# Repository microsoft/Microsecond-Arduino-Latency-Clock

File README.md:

# Microsecond Arduino Due Code and Schematics

Microsecond Arduino Due Code and Schematics accompanying the paper presented in IEEE VR 2020 "Measuring System Visual Latency through Cognitive Latency on Video See-Through AR devices" [1]
https://www.microsoft.com/en-us/research/publication/measuring-system-visual-latency-through-cognitive-latency-on-video-see-through-ar-devices/

The clock starts from zero and continues to displayelapsed time since the device was powered on. The LED turn-on andturn-off time is sub-microsecond [2], therefore we know that ourclock is sufficient for at least 0.1 millisecond measurements as theLEDs turn on and off faster than we are updating the digit segments.

This clock can be then visualized through an external observer [3] using high refresh cameras.

[1] Gruen, R., Ofek, E., Steed, A., Gal, R., Sinclair, M., & Gonzalez-Franco, M. (2020) Measuring System Visual Latency through Cognitive Latency on Video See-Through AR devices. IEEE VR 2020

[2] Lee,T. P. (1975) Effect of junction capacitance on the rise time of led’s and onthe turn-on delay of injection lasers. The Bell System Technical Journal,54(1):53–68, Jan 1975.

[3] Wu, W., Dong, Y., & Hoover, A. (2013). Measuring digital system latency from sensing to actuation at continuous 1-ms resolution. Presence: Teleoperators and Virtual Environments, 22(1), 20-35.

Schematics created with Eagle v 9.5.2.

# Contributing

This project welcomes contributions and suggestions.  Most contributions require you to agree to a
Contributor License Agreement (CLA) declaring that you have the right to, and actually do, grant us
the rights to use your contribution. For details, visit https://cla.opensource.microsoft.com.

When you submit a pull request, a CLA bot will automatically determine whether you need to provide
a CLA and decorate the PR appropriately (e.g., status check, comment). Simply follow the instructions
provided by the bot. You will only need to do this once across all repos using our CLA.

This project has adopted the [Microsoft Open Source Code of Conduct](https://opensource.microsoft.com/codeofconduct/).
For more information see the [Code of Conduct FAQ](https://opensource.microsoft.com/codeofconduct/faq/) or
contact [opencode@microsoft.com](mailto:opencode@microsoft.com) with any additional questions or comments.

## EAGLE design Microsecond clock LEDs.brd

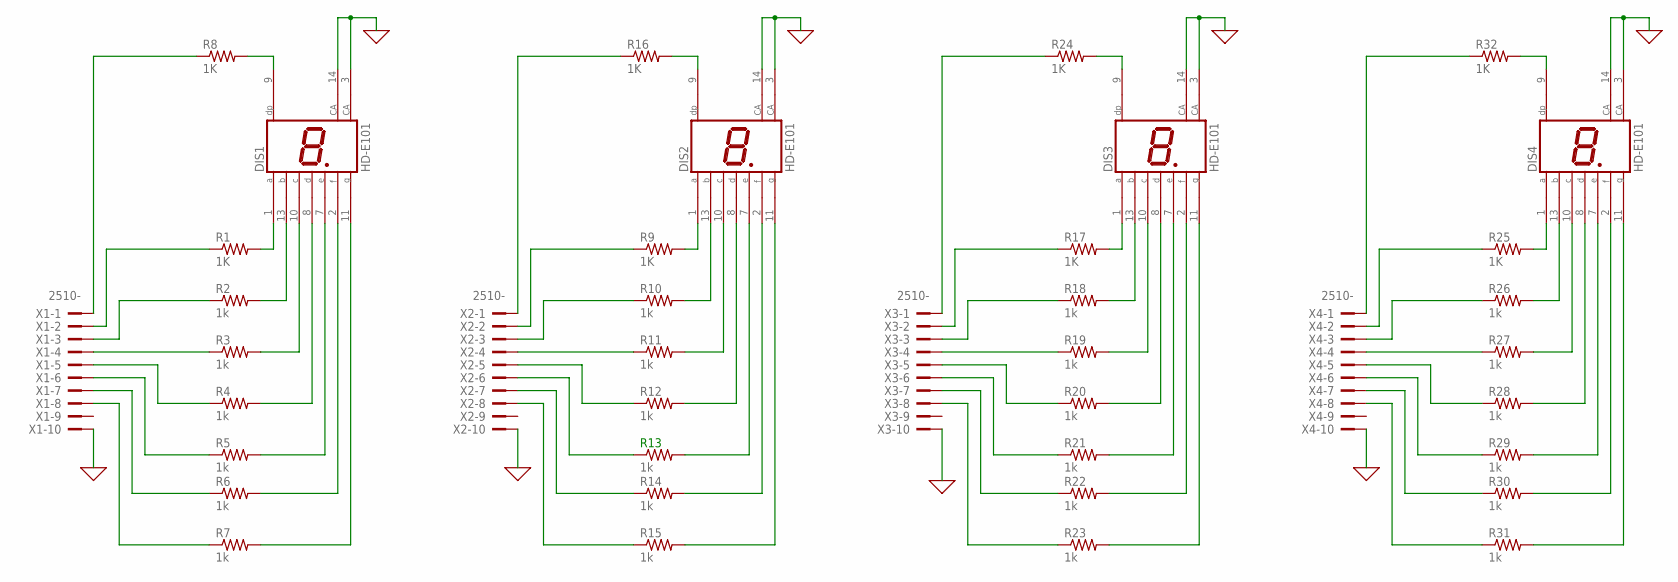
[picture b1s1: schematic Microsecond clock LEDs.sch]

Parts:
DIS1, DIS2, DIS3, DIS4: HD-E101; HDSP-I
R1, R8, R9, R16, R17, R24, R25, R32: 1K; 0207/7
R2, R3, R4, R5, R6, R7, R10, R11, R12, R13, R14, R15, R18, R19, R20, R21, R22, R23, R26, R27, R28, R29, R30, R31: 1k; 0207/7
X1, X2, X3, X4: 2510-; PAK100/2500-10

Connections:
0: DIS1.3 (CA), DIS1.14 (CA), DIS2.3 (CA), DIS2.14 (CA), DIS3.3 (CA), DIS3.14 (CA), DIS4.3 (CA), DIS4.14 (CA), X1.10, X2.10, X3.10, X4.10
unnamed: DIS1.1 (A), R1.2
unnamed: DIS1.13 (B), R2.2
unnamed: DIS1.10 (C), R3.2
unnamed: DIS1.8 (D), R4.2
unnamed: DIS1.7 (E), R5.2
unnamed: DIS1.2 (F), R6.2
unnamed: DIS1.11 (G), R7.2
unnamed: DIS1.9 (DP), R8.2
unnamed: R8.1, X1.1
unnamed: R1.1, X1.2
unnamed: R2.1, X1.3
unnamed: R3.1, X1.4
unnamed: R4.1, X1.5
unnamed: R5.1, X1.6
unnamed: R6.1, X1.7
unnamed: R7.1, X1.8
unnamed: DIS2.1 (A), R9.2
unnamed: DIS2.13 (B), R10.2
unnamed: DIS2.10 (C), R11.2
unnamed: DIS2.8 (D), R12.2
unnamed: DIS2.7 (E), R13.2
unnamed: DIS2.2 (F), R14.2
unnamed: DIS2.11 (G), R15.2
unnamed: DIS2.9 (DP), R16.2
unnamed: R16.1, X2.1
unnamed: R9.1, X2.2
unnamed: R10.1, X2.3
unnamed: R11.1, X2.4
unnamed: R12.1, X2.5
unnamed: R13.1, X2.6
unnamed: R14.1, X2.7
unnamed: R15.1, X2.8
unnamed: DIS3.1 (A), R17.2
unnamed: DIS3.13 (B), R18.2
unnamed: DIS3.10 (C), R19.2
unnamed: DIS3.8 (D), R20.2
unnamed: DIS3.7 (E), R21.2
unnamed: DIS3.2 (F), R22.2
unnamed: DIS3.11 (G), R23.2
unnamed: DIS3.9 (DP), R24.2
unnamed: R24.1, X3.1
unnamed: R17.1, X3.2
unnamed: R18.1, X3.3
unnamed: R19.1, X3.4
unnamed: R20.1, X3.5
unnamed: R21.1, X3.6
unnamed: R22.1, X3.7
unnamed: R23.1, X3.8
unnamed: DIS4.1 (A), R25.2
unnamed: DIS4.13 (B), R26.2
unnamed: DIS4.10 (C), R27.2
unnamed: DIS4.8 (D), R28.2
unnamed: DIS4.7 (E), R29.2
unnamed: DIS4.2 (F), R30.2
unnamed: DIS4.11 (G), R31.2
unnamed: DIS4.9 (DP), R32.2
unnamed: R32.1, X4.1
unnamed: R25.1, X4.2
unnamed: R26.1, X4.3
unnamed: R27.1, X4.4
unnamed: R28.1, X4.5
unnamed: R29.1, X4.6
unnamed: R30.1, X4.7
unnamed: R31.1, X4.8

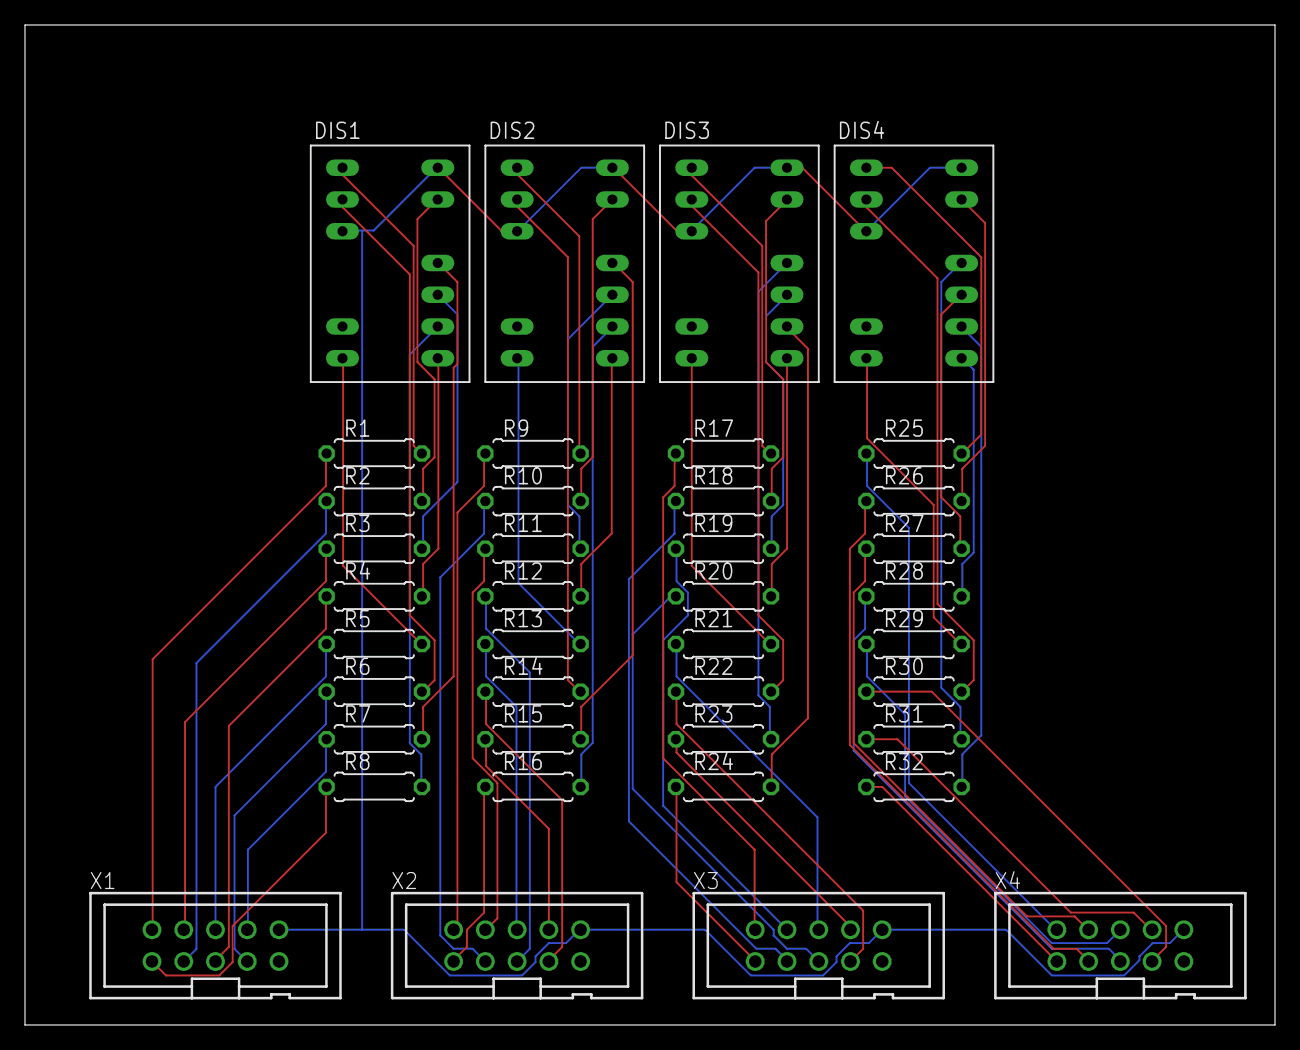
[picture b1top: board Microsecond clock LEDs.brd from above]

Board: 2 copper layers, 100.0 x 80.0 mm, 40 parts (0 on the bottom side), 65 nets.

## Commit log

2020-03-25 Initial CODE_OF_CONDUCT.md commit
2020-03-25 Initial LICENSE commit
2020-03-25 Initial README.md commit
2020-03-25 Initial SECURITY.md commit
2020-03-26 Added Eagle 9.5.2 project files
